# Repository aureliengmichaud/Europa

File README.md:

A simple and practical 4x4 mechanical keypad.

## Features

 * Simple and usable layout.
 * Driven by Arduino Pro Micro.
 * Cheap if using FR-4 plates (PCB material).
 * Awesome looking sandwich case.
 * No LEDs and no underglow.
 * Not another swiss cheese PCB.
 * Fully open source.
 * Powered by [QMK Firmware](https://github.com/qmk/qmk_firmware).

## PCB

### Front

### Back

### Files

 Grab the zip containing the gerbers files needed for manufacturing [here](https://github.com/aureliengmichaud/Europa/blob/master/Europa-PCB-Gerbers-Rev1.zip).

## Plates

### Switch Plate

### Bottom Plate

### Files

 Grab the files needed to get the plates made or modified in KiCad [here](https://github.com/aureliengmichaud/Europa/tree/master/Plates). DXF and SVG files are included, depending on the manufacturer's needs. If you choose to get them made in PCB material (FR-4), you'll find the gerbers for the switch plate [here](https://github.com/aureliengmichaud/Europa/blob/master/Europa-Switch-Plate-Gerbers-Rev1.zip) and the bottom plate [here](https://github.com/aureliengmichaud/Europa/blob/master/Europa-Bottom-Plate-Gerbers-Rev1.zip).

## Parts List

 Part  |  Quantity
 :----  |  :--------:
 [Europa PCB](https://github.com/aureliengmichaud/Europa/blob/master/Europa-PCB-Gerbers-Rev1.zip)  |  1
 [1N4148 Diodes](https://candykeys.com/product/fairchild-semiconductor-diode-1n4148-pack-of-100)  |  16
 [Pro Micro Microcontroller](https://candykeys.com/product/pro-micro-5v-16mhz)  |  1
 [Cherry MX Switches  (or compatible)](https://candykeys.com/category:switches/brand:cherry)  |  16
 [Europa Switch Plate](https://github.com/aureliengmichaud/Europa/tree/master/Plates)  |  1
 [Europa Bottom Plate](https://github.com/aureliengmichaud/Europa/tree/master/Plates)  |  1
 [M3x8 Screws](https://www.ebay.fr/sch/i.html?_odkw=m3x8+screws&_osacat=0&_from=R40&_trksid=m570.l1313&_nkw=m3+screws&_sacat=0)  |  16
 [M3x14 Standoffs](https://www.ebay.fr/sch/i.html?_odkw=m3+screws&_osacat=0&_from=R40&_trksid=m570.l1313&_nkw=m3+standoffs&_sacat=0)  |  8
 [Micro-USB Cable](https://voltacharger.com/products/volta-2-0)  | 1
 [Keycaps](https://www.aliexpress.com/wholesale?catId=0&initiative_id=SB_20200426114303&SearchText=keycaps)  |  16

## Firmware

 The keyboard is powered by [QMK Firmware](https://github.com/qmk/qmk_firmware). You can find the firmware for the Europa [here](https://github.com/aureliengmichaud/Europa/tree/master/Firmware/aureliengmichaud/europa).

 Add the `aureliengmichaud` folder to your own fork of QMK to flash it to your keyboard.

 If you're new to QMK, please take the time to learn all the ins and outs and familiarize yourself with it by reading the [official documentation](https://docs.qmk.fm/#/).

## License

 Released under [MIT License](https://github.com/aureliengmichaud/Europa/blob/master/LICENSE).

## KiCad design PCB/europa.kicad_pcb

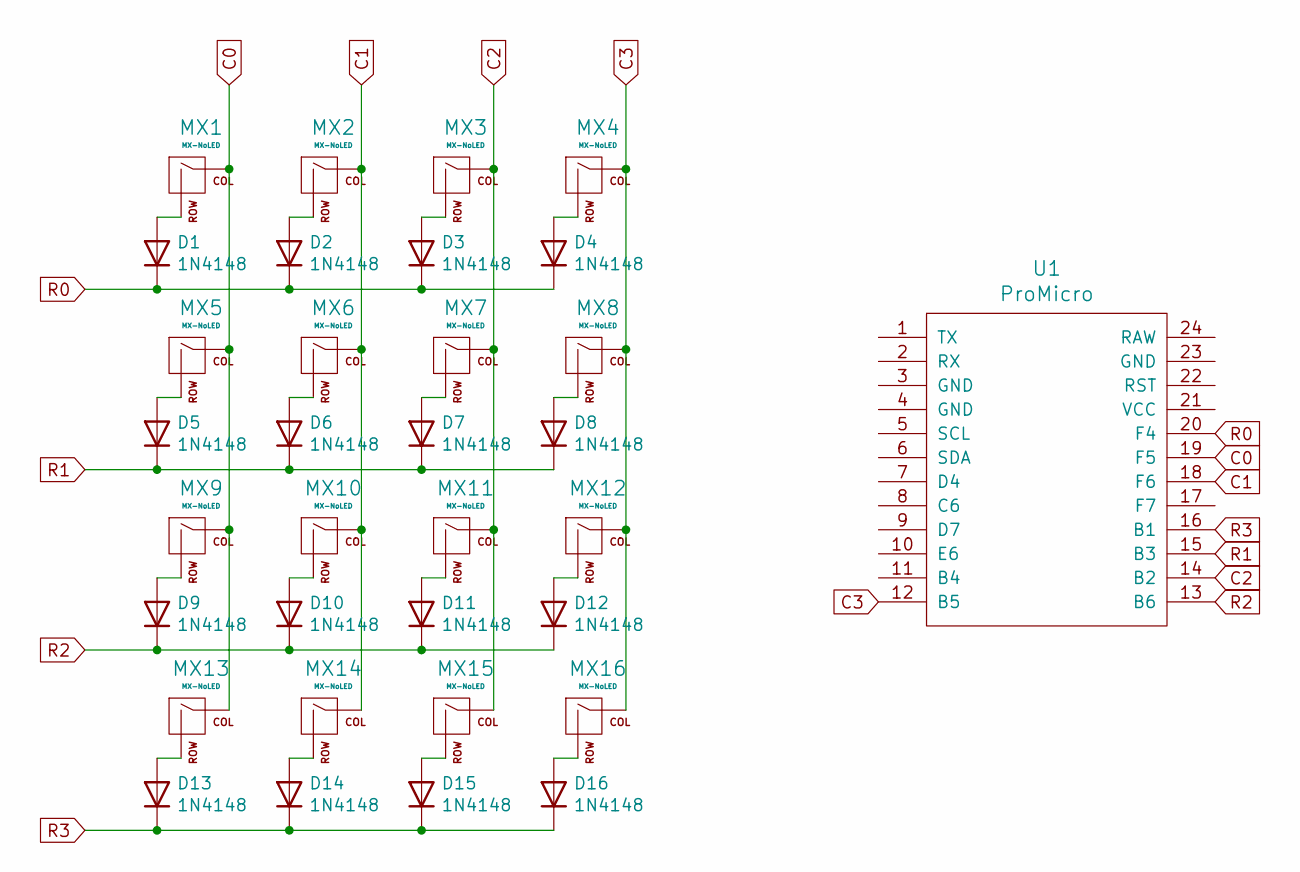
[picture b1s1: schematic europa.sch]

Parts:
D1, D2, D3, D4, D5, D6, D7, D8, D9, D10, D11, D12, D13, D14, D15, D16: 1N4148; D_DO-35_SOD27_P7.62mm_Horizontal
MX1, MX2, MX3, MX4, MX5, MX6, MX7, MX8, MX9, MX10, MX11, MX12, MX13, MX14, MX15, MX16: MX-NoLED; MXOnly-1U-NoLED
U1: ProMicro

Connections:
C0: MX1.1 (COL), MX5.1 (COL), MX9.1 (COL), MX13.1 (COL), U1.19 (F5)
C1: MX2.1 (COL), MX6.1 (COL), MX10.1 (COL), MX14.1 (COL), U1.18 (F6)
C2: MX3.1 (COL), MX7.1 (COL), MX11.1 (COL), MX15.1 (COL), U1.14 (B2)
C3: MX4.1 (COL), MX8.1 (COL), MX12.1 (COL), MX16.1 (COL), U1.12 (B5)
unnamed: D1.2 (A), MX1.2 (ROW)
unnamed: D2.2 (A), MX2.2 (ROW)
unnamed: D3.2 (A), MX3.2 (ROW)
unnamed: D4.2 (A), MX4.2 (ROW)
unnamed: D5.2 (A), MX5.2 (ROW)
unnamed: D6.2 (A), MX6.2 (ROW)
unnamed: D7.2 (A), MX7.2 (ROW)
unnamed: D8.2 (A), MX8.2 (ROW)
unnamed: D9.2 (A), MX9.2 (ROW)
unnamed: D10.2 (A), MX10.2 (ROW)
unnamed: D11.2 (A), MX11.2 (ROW)
unnamed: D12.2 (A), MX12.2 (ROW)
unnamed: D13.2 (A), MX13.2 (ROW)
unnamed: D14.2 (A), MX14.2 (ROW)
unnamed: D15.2 (A), MX15.2 (ROW)
unnamed: D16.2 (A), MX16.2 (ROW)
R0: D1.1 (K), D2.1 (K), D3.1 (K), D4.1 (K), U1.20 (F4)
R1: D5.1 (K), D6.1 (K), D7.1 (K), D8.1 (K), U1.15 (B3)
R2: D9.1 (K), D10.1 (K), D11.1 (K), D12.1 (K), U1.13 (B6)
R3: D13.1 (K), D14.1 (K), D15.1 (K), D16.1 (K), U1.16 (B1)

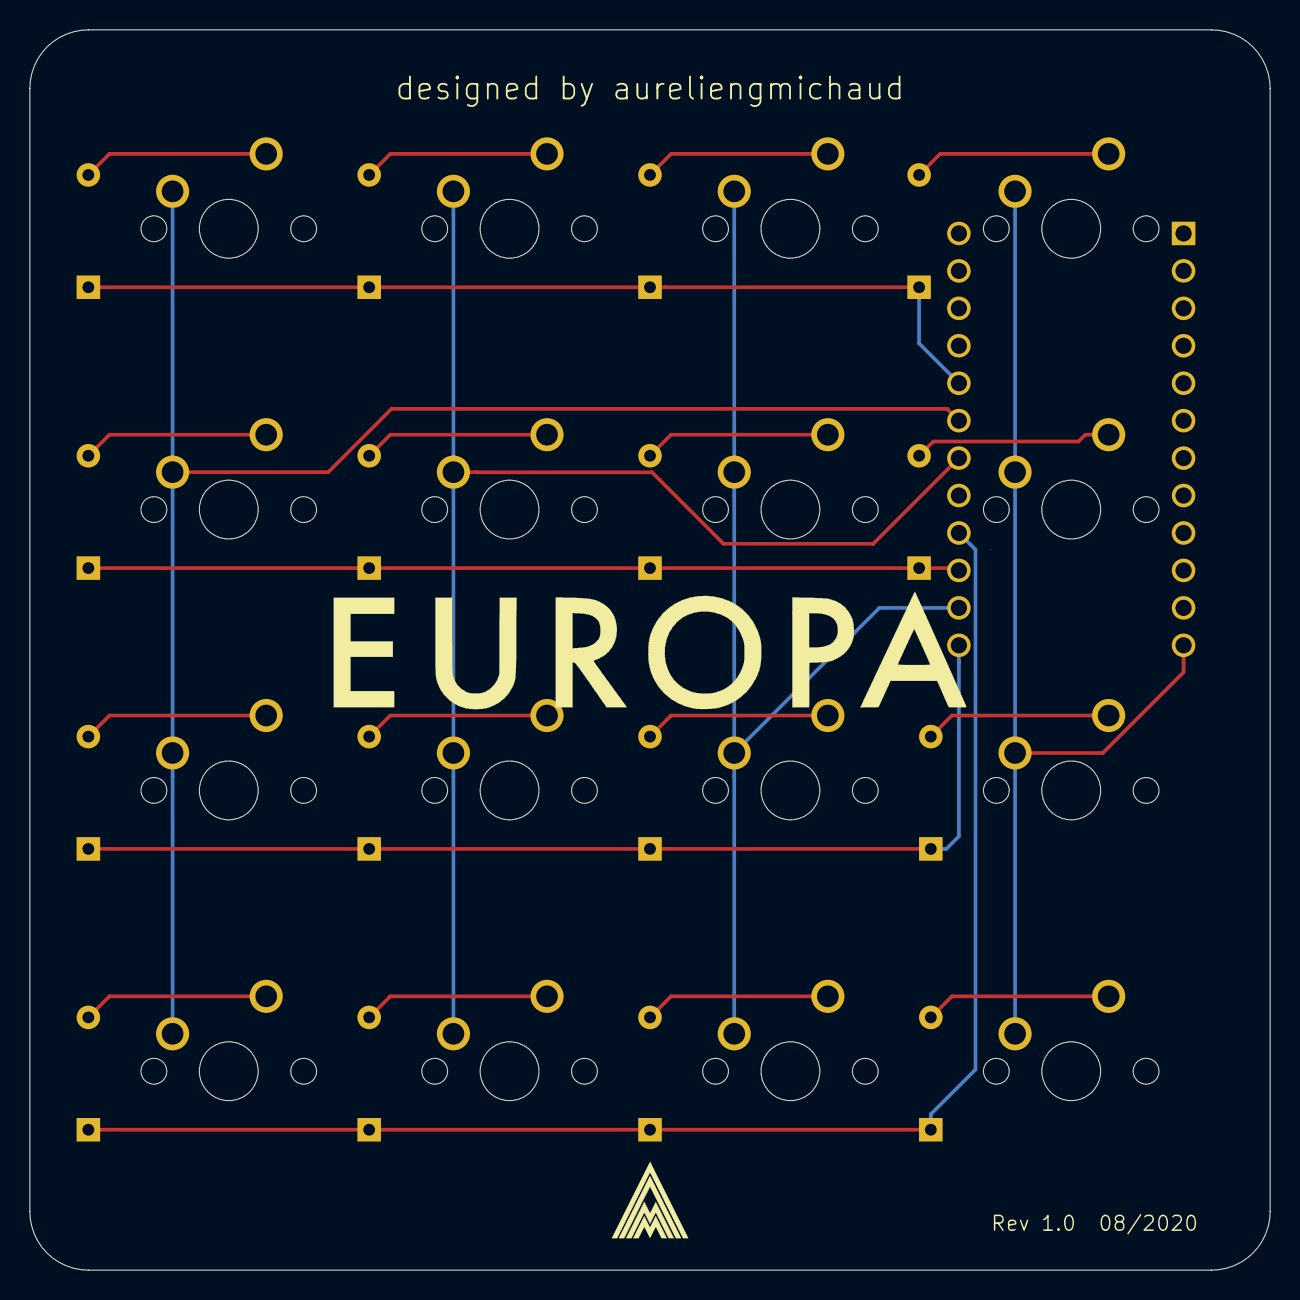
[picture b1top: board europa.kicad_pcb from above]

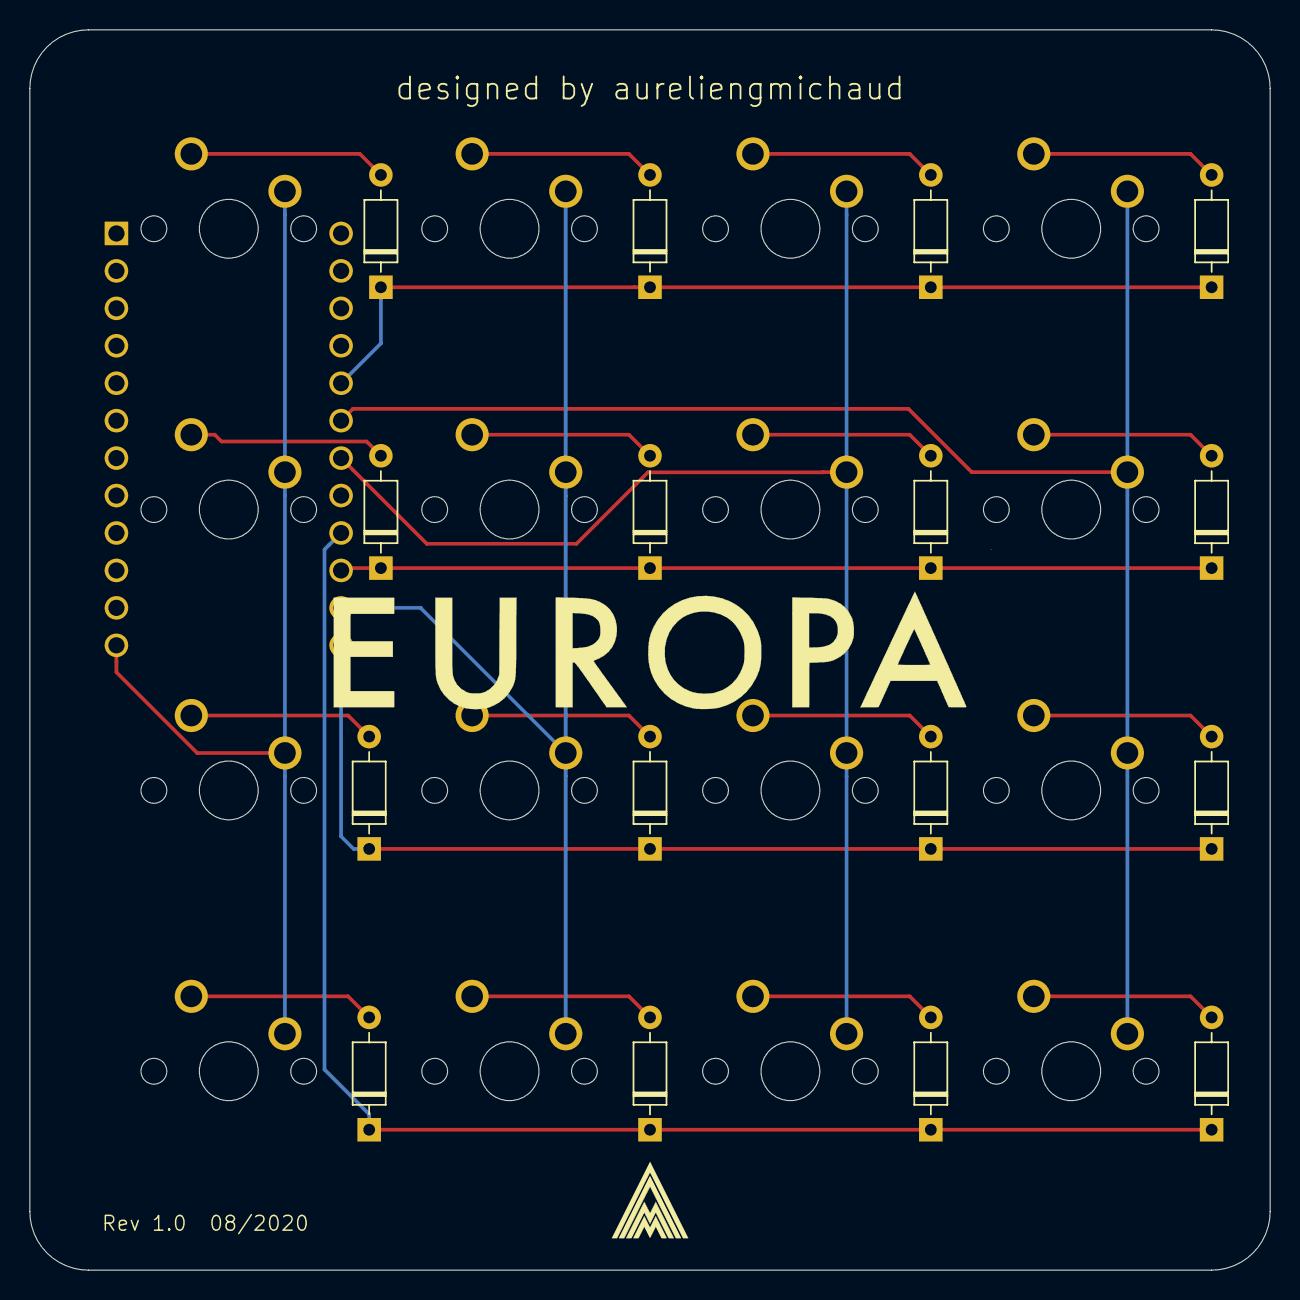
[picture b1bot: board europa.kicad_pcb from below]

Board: 2 copper layers, 84.1 x 84.1 mm, 33 parts (17 on the bottom side), 24 nets.

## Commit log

2020-08-27 Add PCB & Plates
2020-08-27 Add PCB / Plates
2020-08-27 Update PCB Gerbers
2020-08-27 Update Plates
2020-09-14 Update Europa
2021-03-28 Add Firmware
2021-03-28 Update Firmware
2021-11-14 DS_Store
